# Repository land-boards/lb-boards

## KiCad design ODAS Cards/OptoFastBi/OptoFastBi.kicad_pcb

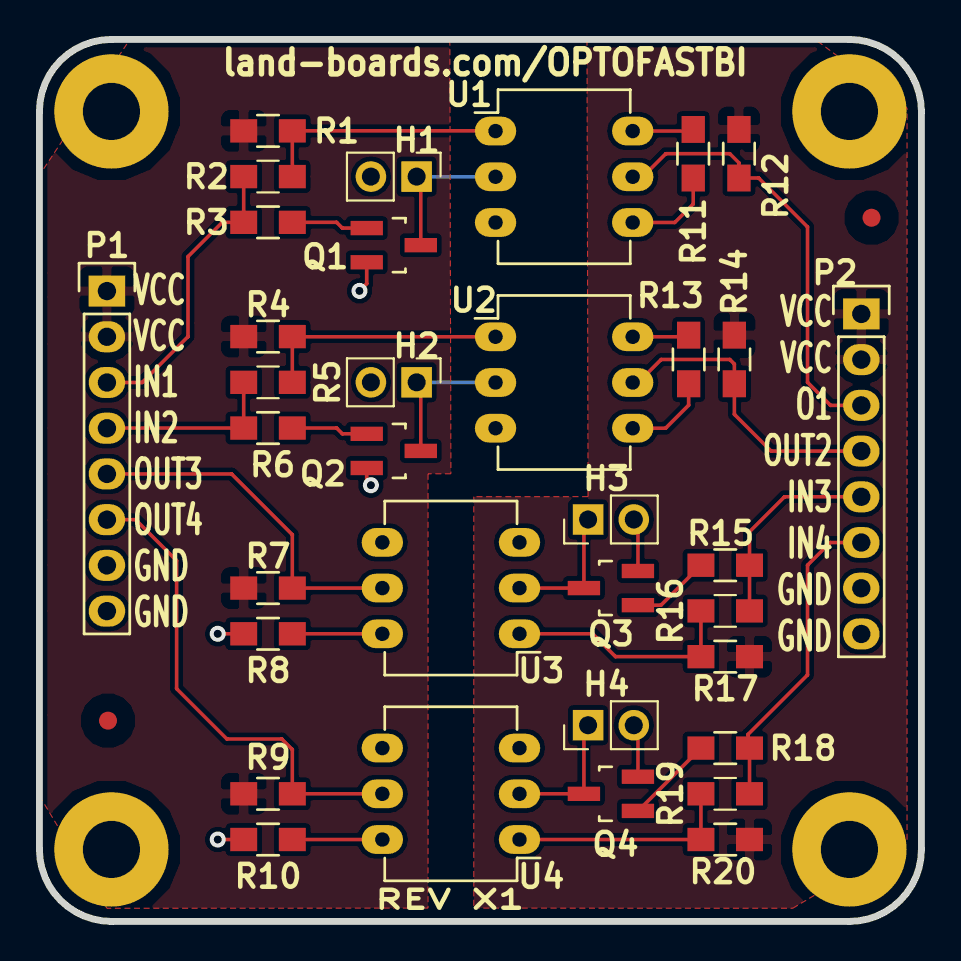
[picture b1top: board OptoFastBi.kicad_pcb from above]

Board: 32 copper layers, 49.0 x 49.0 mm, 41 parts (0 on the bottom side), 28 nets.

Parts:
FID1, FID2: ADAFRUIT_FIDUCIAL; FIDUCIAL
H1, H2, H3, H4: DNP; Pin_Header_Straight_1x02_Pitch2.54mm
MTG1, MTG2, MTG3, MTG4: MTG_HOLE; MTG-4-40
P1, P2: CONN_01X08; Pin_Header_Straight_1x08
Q1, Q2, Q3, Q4: DNP(2N3904); SOT-23_Handsoldering
R1, R4, R17, R20: 150; R_0805_HandSoldering
R2, R5, R16, R19: DNP; R_0805_HandSoldering
R3, R6, R15, R18: 10K; R_0805_HandSoldering
R7, R9, R12, R14: 1.2K; R_0805_HandSoldering
R8, R10, R11, R13: 20K; R_0805_HandSoldering
TEST: COUPON; TEST_BLK-REAR
U1, U2, U3, U4: 4N26; DIP-6_W7.62mm_LongPads

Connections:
/GNDL: H1.2, H2.2, P1.7, P1.8, Q1.2, Q2.2, R8.2, R10.2, U3.4, U4.4
/GNDR: H3.2, H4.2, P2.7, P2.8, Q3.2, Q4.2, R11.2, R13.2, U1.4, U2.4
/IN1: P1.3, R2.1, R3.1
/IN2: P1.4, R5.1, R6.1
/IN3: P2.5, R15.1, R16.1
/IN4: P2.6, R18.1, R19.1
/OUT1: P2.3, R12.1, U1.5
/OUT2: P2.4, R14.1, U2.5
/OUT3: P1.5, R7.1, U3.5
/OUT4: P1.6, R9.1, U4.5
/VCCL: P1.1, P1.2, R1.1, R4.1, R7.2, R9.2
/VCCR: P2.1, P2.2, R12.2, R14.2, R17.1, R20.1
unnamed: H1.1, Q1.3, U1.2
unnamed: H2.1, Q2.3, U2.2
unnamed: H3.1, Q3.3, U3.2
unnamed: H4.1, Q4.3, U4.2
unnamed: Q1.1, R3.2
unnamed: Q2.1, R6.2
unnamed: Q3.1, R15.2
unnamed: Q4.1, R18.2
unnamed: R1.2, R2.2, U1.1
unnamed: R4.2, R5.2, U2.1
unnamed: R8.1, U3.6
unnamed: R10.1, U4.6
unnamed: R11.1, U1.6
unnamed: R13.1, U2.6
unnamed: R16.2, R17.2, U3.1
unnamed: R19.2, R20.2, U4.1

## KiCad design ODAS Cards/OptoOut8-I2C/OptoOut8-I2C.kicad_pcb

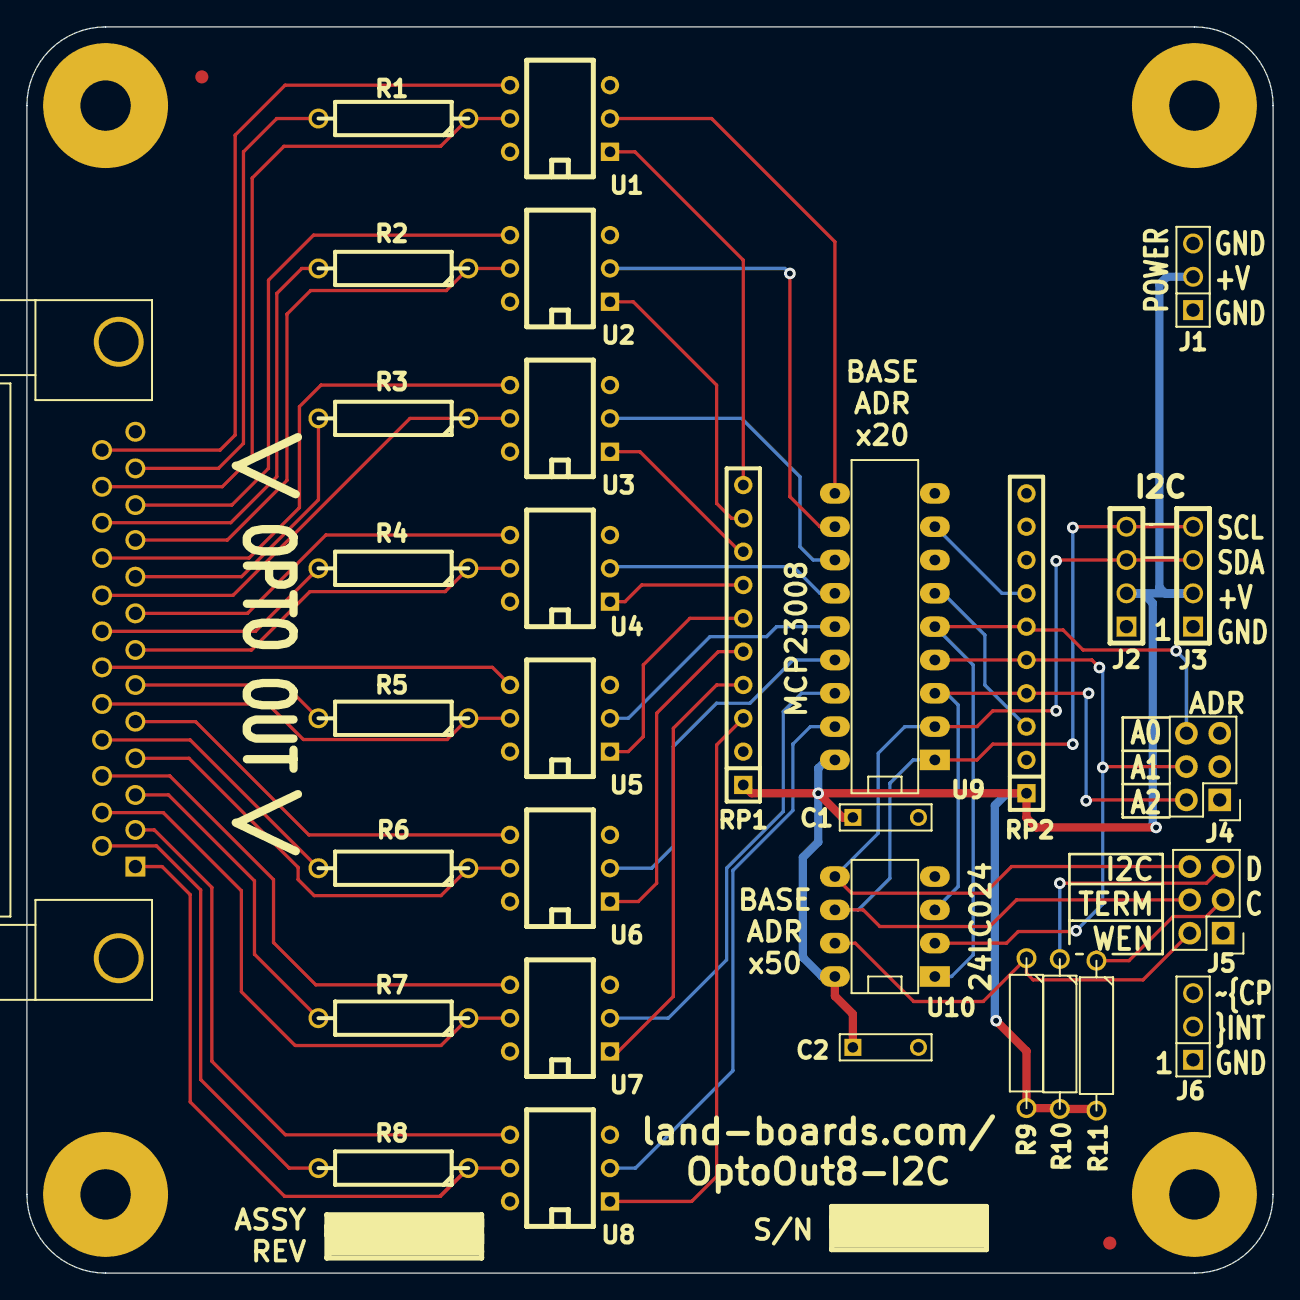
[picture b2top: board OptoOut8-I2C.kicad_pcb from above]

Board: 2 copper layers, 95.0 x 95.0 mm, 40 parts (0 on the bottom side), 52 nets.

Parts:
C1, C2: 0.1uF; C_Rect_L7_W2_P5
FID1, FID2: ADAFRUIT_FIDUCIAL; FIDUCIAL
J1, J6: CONN_3; PIN_ARRAY_3X1
J2, J3: CONN_4; pin_array_4x1
J4: CONN_3X2; Pin_Header_Straight_2x03
J5: CONN_02X03; Pin_Header_Straight_2x03
J7: DB25; DB25FC
MTG1, MTG2, MTG3, MTG4: MTG_HOLE; MTG-6-32
R1, R2, R3, R4, R5, R6, R7, R8: 4.7K; R4-5
R9: 1K; R4-5
R10, R11: 2.2K; R4-5
RP1: 330-RPACK; SIL-10
RP2: 4.7K-RPACK; SIL-10
ST1, ST2: CONN_1; REV_BLOCK
U1, U2, U3, U4, U5, U6, U7, U8: 4N26; DIP-6__300
U9: MCP23008P; DIP-18__300_ELL
U10: 24C01; DIP-8__300_ELL

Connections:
/A0: J4.6, RP2.6, U9.5, U10.1
/A1: J4.4, RP2.5, U9.4, U10.2
/A2: J4.2, RP2.4, U9.3, U10.3
/G0: J7.25, U1.4
/G1: J7.11, U2.4
/G2: J7.22, U3.4
/G3: J7.8, U4.4
/G4: J7.19, U5.4
/G5: J7.5, U6.4
/G6: J7.16, U7.4
/G7: J7.2, U8.4
/S0: J7.24, R1.1, U1.5
/S1: J7.10, R2.1, U2.5
/S2: J7.21, R3.1, U3.5
/S3: J7.7, R4.1, U4.5
/S4: J7.18, R5.1, U5.5
/S5: J7.4, R6.1, U6.5
/S6: J7.15, R7.1, U7.5
/S7: J7.1, R8.1, U8.5
/SCL: J2.4, J3.4, J5.4, U9.1, U10.6
/SDA: J2.3, J3.3, J5.6, U9.2, U10.5
/V0: J7.12, R1.2
/V1: J7.23, R2.2
/V2: J7.9, R3.2
/V3: J7.20, R4.2
/V4: J7.6, R5.2
/V5: J7.17, R6.2
/V6: J7.3, R7.2
/V7: J7.14, R8.2
/VCC: C1.1, C2.1, J1.2, J2.2, J3.2, R9.2, R10.2, R11.2, RP1.1, RP2.1, U9.18, U10.8
GND: C1.2, C2.2, J1.1, J1.3, J2.1, J3.1, J4.1, J4.3, J4.5, J5.1, J6.1, J6.3, U9.9, U10.4
unnamed: J5.2, R9.1, U10.7
unnamed: J5.3, R11.1
unnamed: J5.5, R10.1
unnamed: RP1.3, U8.1
unnamed: RP1.4, U7.1
unnamed: RP1.5, U6.1
unnamed: RP1.6, U5.1
unnamed: RP1.7, U4.1
unnamed: RP1.8, U3.1
unnamed: RP1.9, U2.1
unnamed: RP1.10, U1.1
unnamed: RP2.3, U9.6
unnamed: RP2.7, U9.8
unnamed: U1.2, U9.10
unnamed: U2.2, U9.11
unnamed: U3.2, U9.12
unnamed: U4.2, U9.13
unnamed: U5.2, U9.14
unnamed: U6.2, U9.15
unnamed: U7.2, U9.16
unnamed: U8.2, U9.17

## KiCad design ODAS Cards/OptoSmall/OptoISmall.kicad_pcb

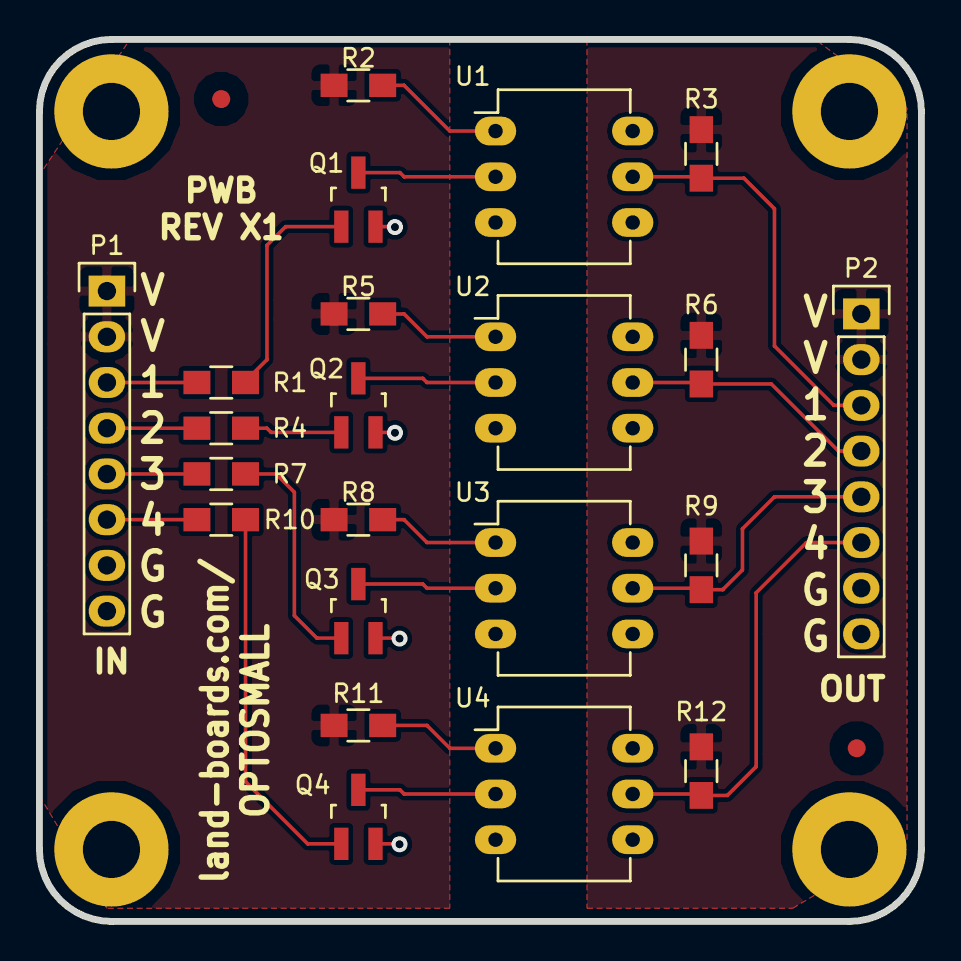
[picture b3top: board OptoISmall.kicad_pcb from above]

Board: 2 copper layers, 49.0 x 49.0 mm, 29 parts (1 on the bottom side), 24 nets.

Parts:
FID1, FID2: ADAFRUIT_FIDUCIAL; FIDUCIAL
MTG1, MTG2, MTG3, MTG4: MTG_HOLE; MTG-4-40
P1, P2: CONN_01X08; Pin_Header_Straight_1x08
Q1, Q2, Q3, Q4: 2N3904; SOT-23_Handsoldering
R1, R4, R7, R10: 10K; R_0805_HandSoldering
R2, R5, R8, R11: 150; R_0805_HandSoldering
R3, R6, R9, R12: 1.2K; R_0805_HandSoldering
ST1: CONN_1; REV_BLOCK
U1, U2, U3, U4: 4N26; DIP-6_W7.62mm_LongPads

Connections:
/OptoBlk1/GND1: P1.7, P1.8, Q1.2, Q2.2, Q3.2, Q4.2
/OptoBlk1/GND2: P2.7, P2.8, U1.4, U2.4, U3.4, U4.4
/OptoBlk1/IN1: P1.3, R1.1
/OptoBlk1/OUT: P2.3, R3.1, U1.5
/OptoBlk1/VCC1: P1.1, P1.2, R2.1, R5.1, R8.1, R11.1
/OptoBlk1/VCC2: P2.1, P2.2, R3.2, R6.2, R9.2, R12.2
/OptoBlk2/IN1: P1.4, R4.1
/OptoBlk2/OUT: P2.4, R6.1, U2.5
/OptoBlk3/IN1: P1.5, R7.1
/OptoBlk3/OUT: P2.5, R9.1, U3.5
/OptoBlk4/IN1: P1.6, R10.1
/OptoBlk4/OUT: P2.6, R12.1, U4.5
unnamed: Q1.1, R1.2
unnamed: Q1.3, U1.2
unnamed: Q2.1, R4.2
unnamed: Q2.3, U2.2
unnamed: Q3.1, R7.2
unnamed: Q3.3, U3.2
unnamed: Q4.1, R10.2
unnamed: Q4.3, U4.2
unnamed: R2.2, U1.1
unnamed: R5.2, U2.1
unnamed: R8.2, U3.1
unnamed: R11.2, U4.1

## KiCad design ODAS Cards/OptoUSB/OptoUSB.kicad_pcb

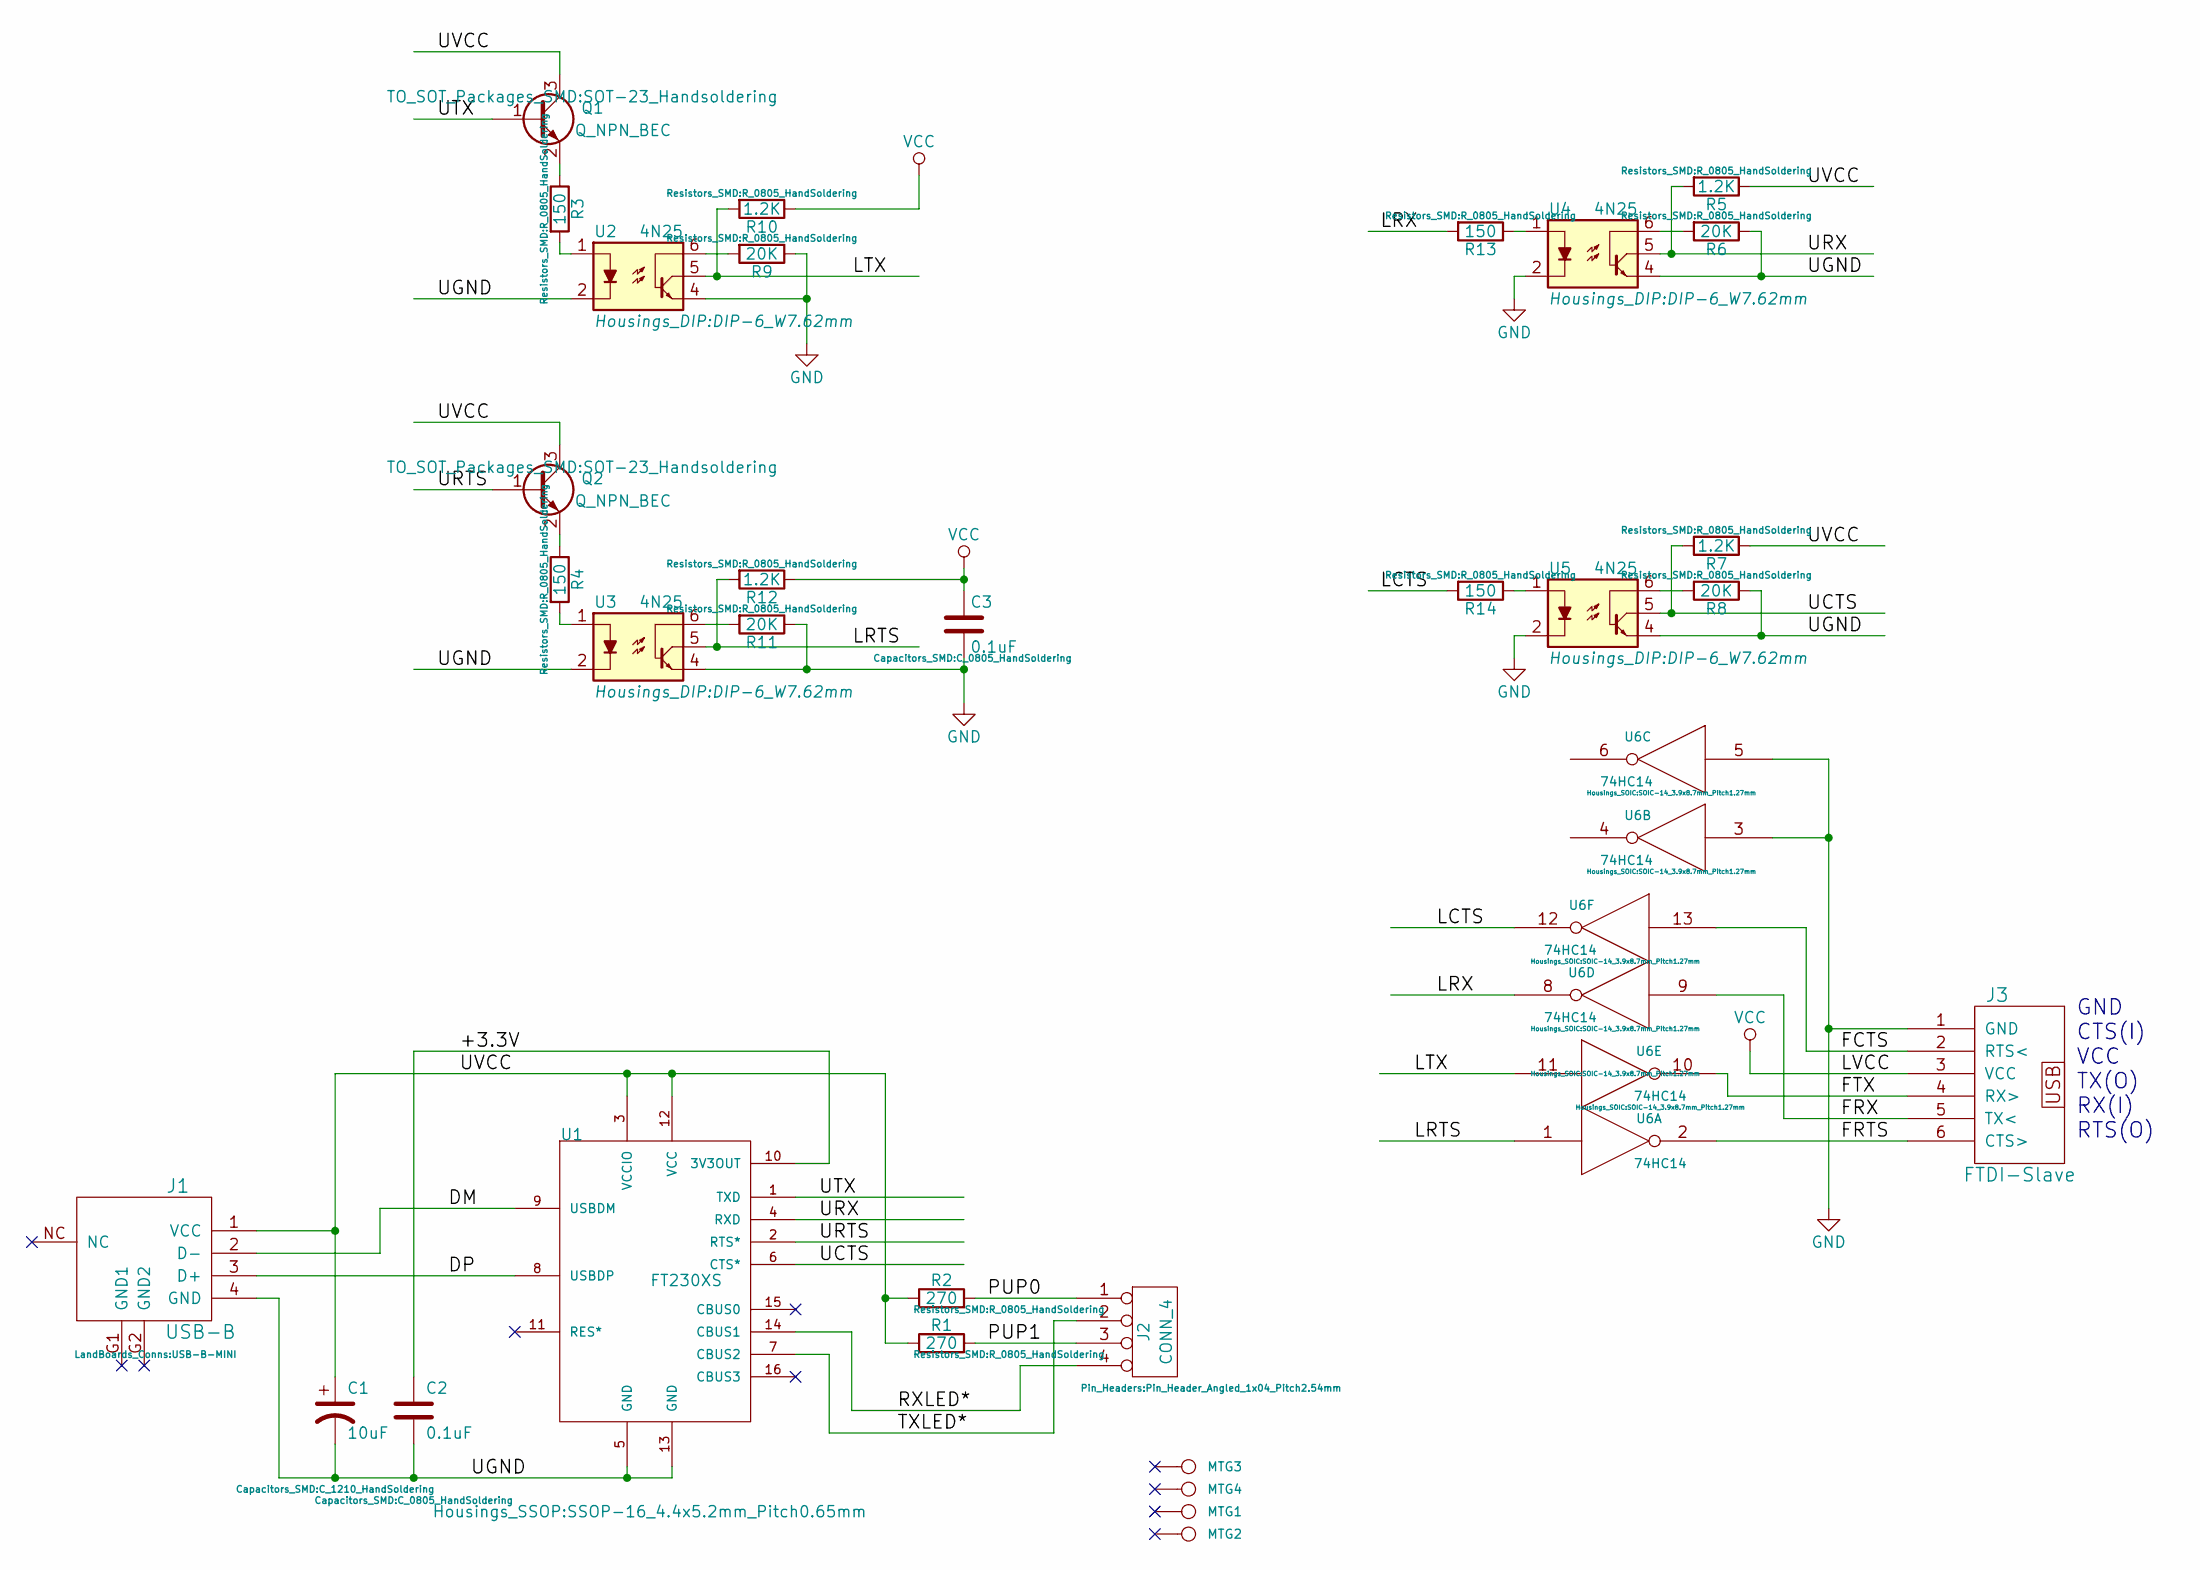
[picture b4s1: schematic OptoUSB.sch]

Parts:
C1: 10uF; C_1210_HandSoldering; MfgPN CC121ZKY5V8BB106
C2: 0.1uF; C_0805_HandSoldering; MfgPN GRM155F51E104ZA1J
C3: 0.1uF; C_0805_HandSoldering
J1: USB-B; USB-B-MINI; MfgPN UX60SC-MB-5ST(80)
J2: CONN_4; Pin_Header_Angled_1x04_Pitch2.54mm
J3: FTDI-Slave
MTG1, MTG3: CONN_1; MTG-4-40; MfgPN N/A
MTG2, MTG4: CONN_1; MTG-4-40
Q1, Q2: Q_NPN_BEC; SOT-23_Handsoldering
R1: 270; R_0805_HandSoldering
R2: 270; R_0805_HandSoldering; MfgPN CRG0805F270R
R3, R4, R13, R14: 150; R_0805_HandSoldering
R5, R7, R10, R12: 1.2K; R_0805_HandSoldering
R6, R8, R9, R11: 20K; R_0805_HandSoldering
U1: FT230XS; SSOP-16_4.4x5.2mm_Pitch0.65mm
U2, U3, U4, U5: 4N25; DIP-6_W7.62mm
U6: 74HC14; SOIC-14_3.9x8.7mm_Pitch1.27mm

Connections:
/+3.3V: C2.1, U1.10 (3V3OUT)
/DM: J1.2 (D-), U1.9 (USBDM)
/DP: J1.3 (D+), U1.8 (USBDP)
/FCTS: J3.2 (RTS<), U6.13
/FRTS: J3.6 (CTS>), U6.2
/FRX: J3.5 (TX<), U6.9
/FTX: J3.4 (RX>), U6.10
/LCTS: R14.2, U6.12
/LRTS: R12.2, U3.5, U6.1
/LRX: R13.2, U6.8
/LTX: R10.2, U2.5, U6.11
/PUP0: J2.1, R2.2
/PUP1: J2.3, R1.2
/RXLED*: J2.4, U1.14 (CBUS1)
/TXLED*: J2.2, U1.7 (CBUS2)
/UCTS: R7.2, U1.6 (CTS*), U5.5
/UGND: C1.2, C2.2, J1.4 (GND), R6.1, R8.1, U1.5 (GND), U1.13 (GND), U2.2, U3.2, U4.4, U5.4
/URTS: Q2.1 (B), U1.2 (RTS*)
/URX: R5.2, U1.4 (RXD), U4.5
/UTX: Q1.1 (B), U1.1 (TXD)
/UVCC: C1.1, J1.1 (VCC), Q1.3 (C), Q2.3 (C), R1.1, R2.1, R5.1, R7.1, U1.3 (VCCIO), U1.12 (VCC)
GND: C3.2, J3.1 (GND), R9.1, R11.1, U2.4, U3.4, U4.2, U5.2, U6.3, U6.5, U6.7 (GND)
unnamed: Q1.2 (E), R3.1
unnamed: Q2.2 (E), R4.1
unnamed: R3.2, U2.1
unnamed: R4.2, U3.1
unnamed: R6.2, U4.6
unnamed: R8.2, U5.6
unnamed: R9.2, U2.6
unnamed: R11.2, U3.6
unnamed: R13.1, U4.1
unnamed: R14.1, U5.1
VCC: C3.1, J3.3 (VCC), R10.1, R12.1, U6.14 (VCC)

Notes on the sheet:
GND CTS(I) VCC TX(O) RX(I) RTS(O)

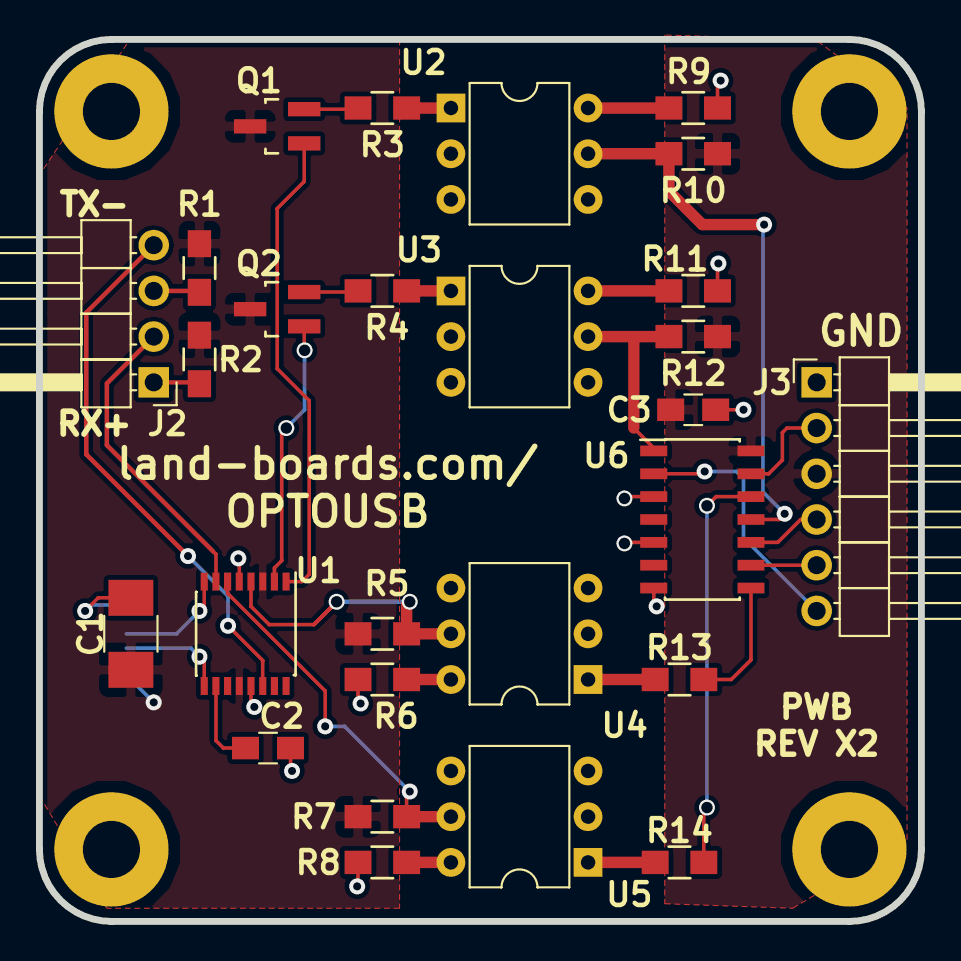
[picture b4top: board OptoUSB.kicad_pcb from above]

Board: 2 copper layers, 49.0 x 49.0 mm, 32 parts (1 on the bottom side), 33 nets.

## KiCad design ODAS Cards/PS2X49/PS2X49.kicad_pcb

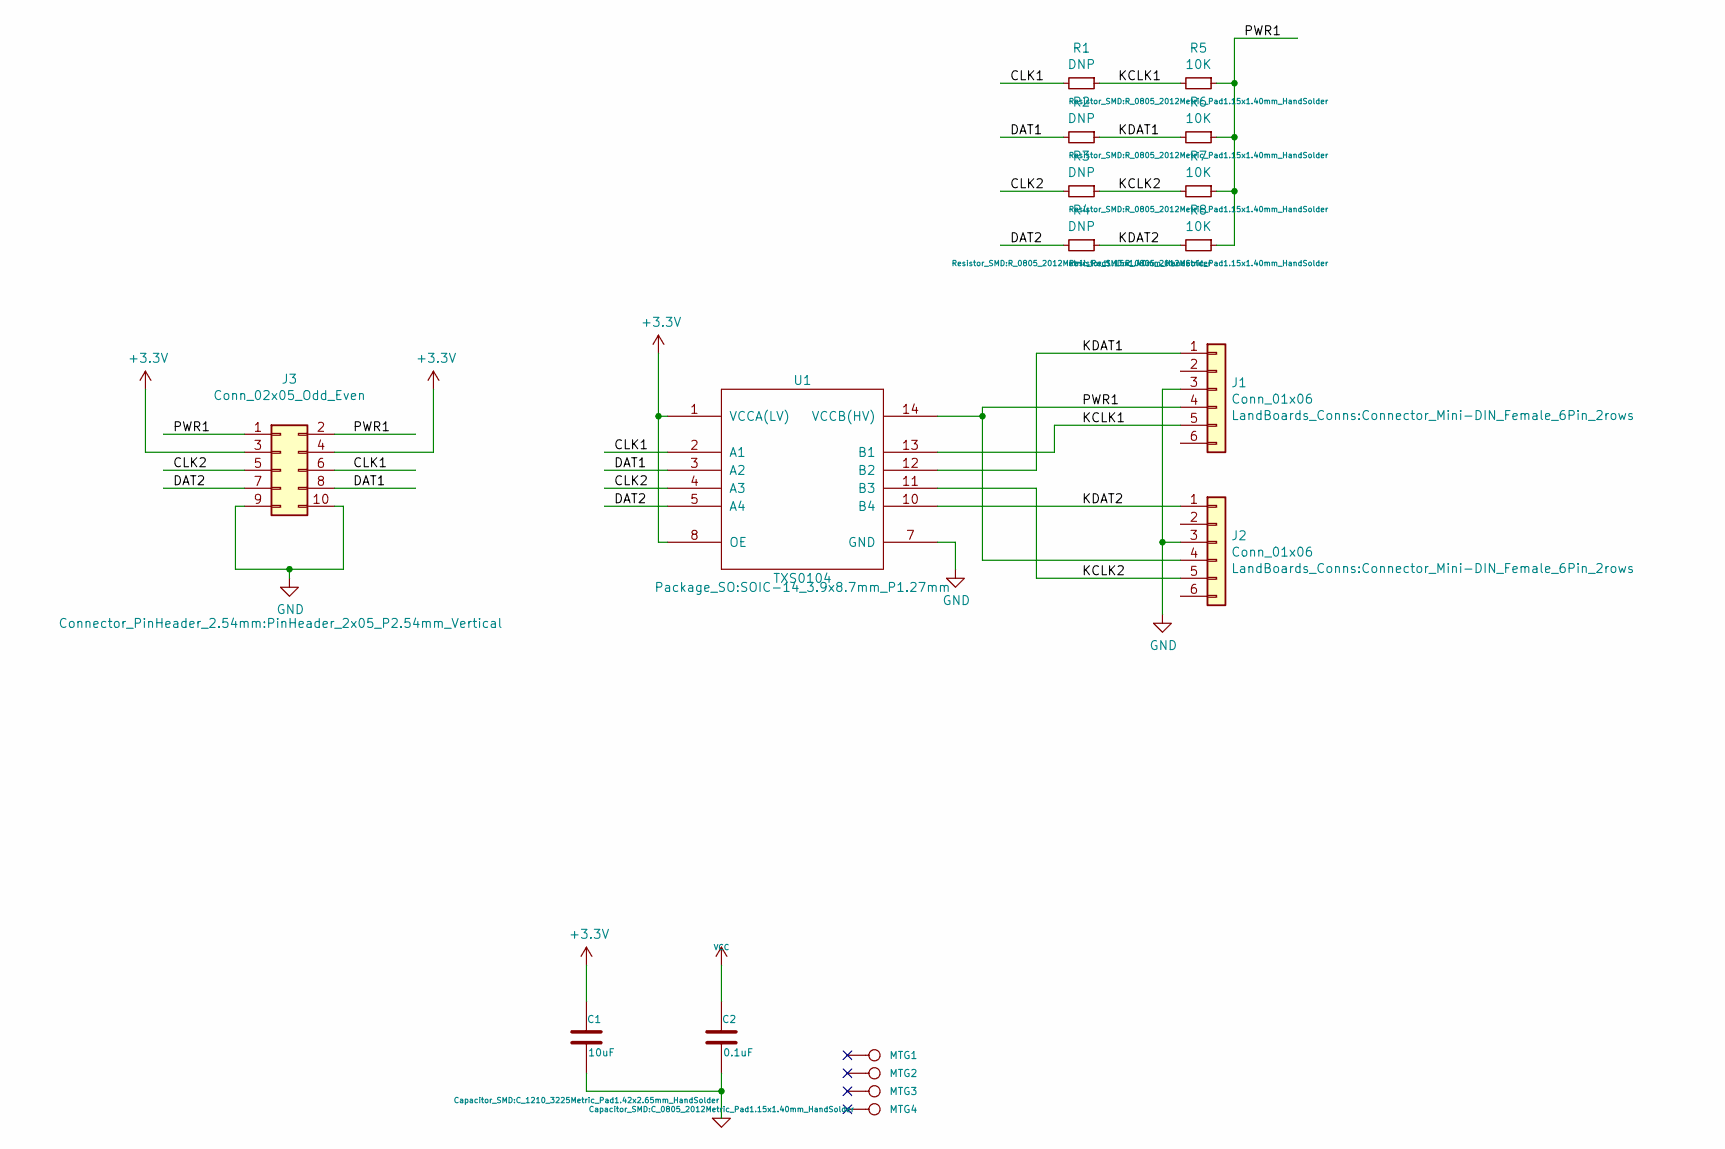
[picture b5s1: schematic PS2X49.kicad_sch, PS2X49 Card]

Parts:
C1: 10uF; C_1210_3225Metric_Pad1.42x2.65mm_HandSolder
C2: 0.1uF; C_0805_2012Metric_Pad1.15x1.40mm_HandSolder
J1, J2: Conn_01x06; Connector_Mini-DIN_Female_6Pin_2rows
J3: Conn_02x05_Odd_Even; PinHeader_2x05_P2.54mm_Vertical
MTG1, MTG2, MTG3, MTG4: CONN_1; MTG-4-40
R1, R2, R3, R4: DNP; R_0805_2012Metric_Pad1.15x1.40mm_HandSolder
R5, R6, R7, R8: 10K; R_0805_2012Metric_Pad1.15x1.40mm_HandSolder
U1: TXS0104; SOIC-14_3.9x8.7mm_P1.27mm

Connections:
+3V3: C1.1, J3.3, J3.4, U1.1 (VCCA(LV)), U1.8 (OE)
/CLK1: J3.6, R1.2, U1.2 (A1)
/CLK2: J3.5, R3.2, U1.4 (A3)
/DAT1: J3.8, R2.2, U1.3 (A2)
/DAT2: J3.7, R4.2, U1.5 (A4)
/KCLK1: J1.5, R1.1, R5.2, U1.13 (B1)
/KCLK2: J2.5, R3.1, R7.2, U1.11 (B3)
/KDAT1: J1.1, R2.1, R6.2, U1.12 (B2)
/KDAT2: J2.1, R4.1, R8.2, U1.10 (B4)
/PWR1: J1.4, J2.4, J3.1, J3.2, R5.1, R6.1, R7.1, R8.1, U1.14 (VCCB(HV))
GND: C1.2, C2.2, J1.3, J2.3, J3.9, J3.10, U1.7 (GND)
VCC: C2.1

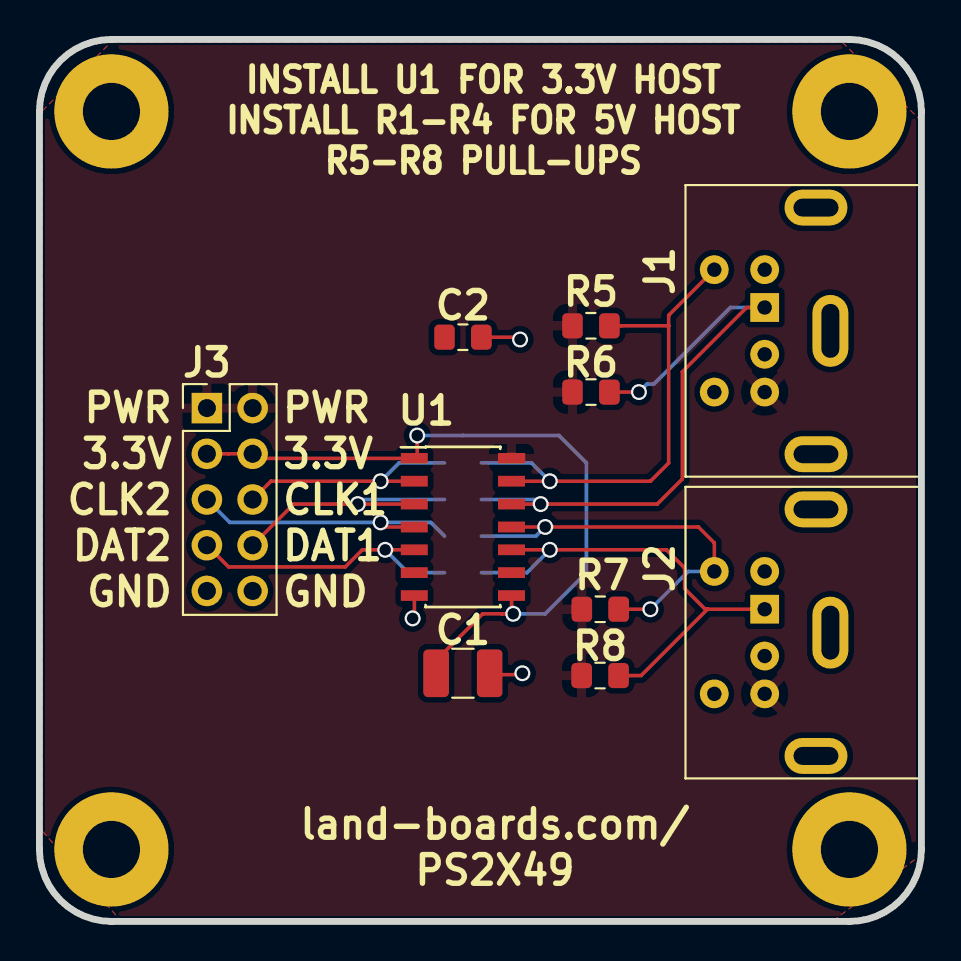
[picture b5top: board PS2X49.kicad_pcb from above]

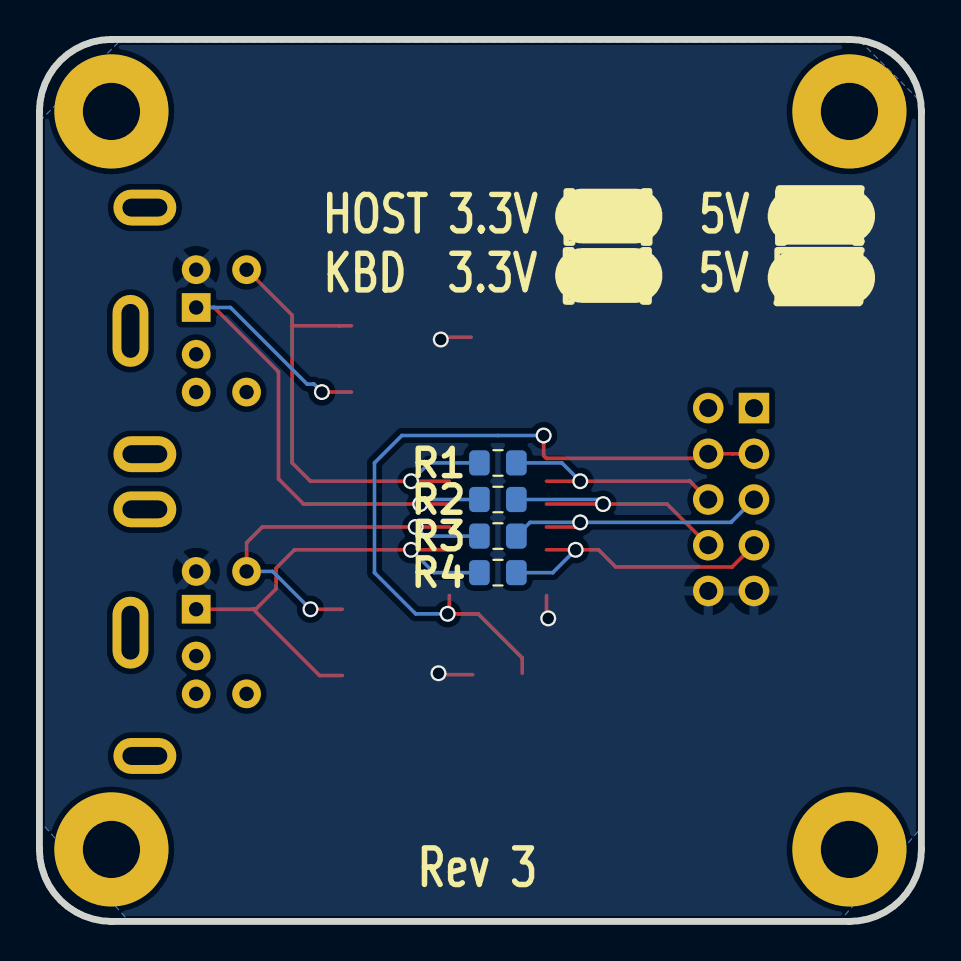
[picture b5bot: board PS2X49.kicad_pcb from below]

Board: 2 copper layers, 49.0 x 49.0 mm, 18 parts (4 on the bottom side), 11 nets.

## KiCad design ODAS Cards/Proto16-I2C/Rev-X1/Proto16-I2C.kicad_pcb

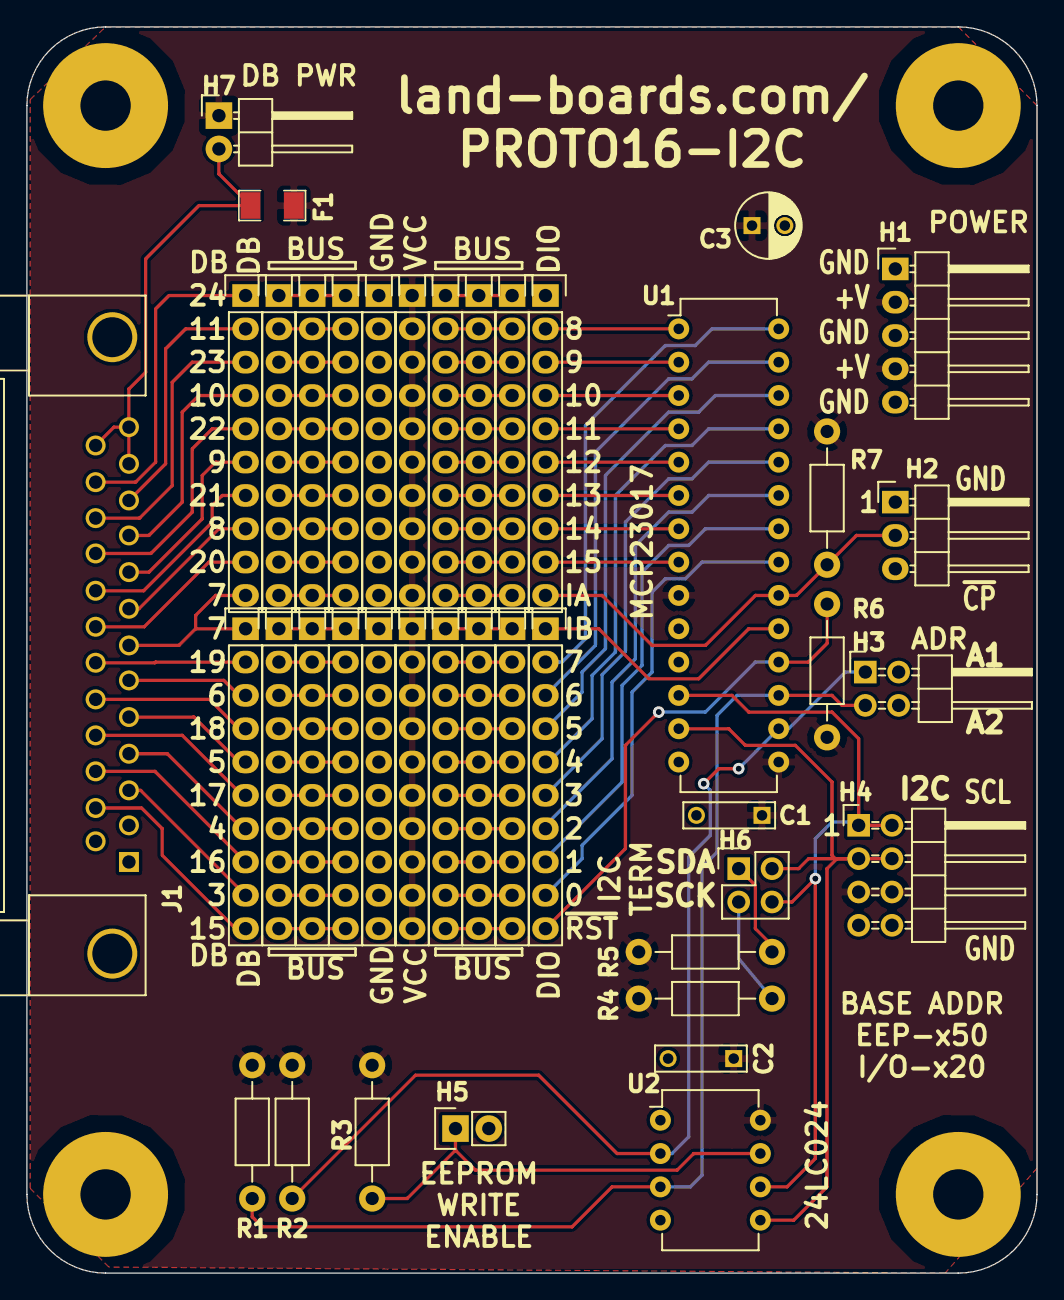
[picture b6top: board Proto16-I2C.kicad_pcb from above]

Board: 2 copper layers, 77.0 x 95.0 mm, 46 parts (0 on the bottom side), 88 nets.

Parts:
C1, C2: 0.1uF; C_Rect_L7_W2_P5
C3: 47uF; C_Radial_D5_L11_P2.5
F1: FUSE; SM1206
H1: CONN_01X05; Pin_Header_Angled_1x05
H2: CONN_01X03; Pin_Header_Angled_1x03
H3: CONN_02X02; Pin_Header_Angled_2x02
H4: CONN_02X04; Pin_Header_Angled_2x04
H5: CONN_01X02; Pin_Header_Straight_1x02
H6: CONN_02X02; Pin_Header_Straight_2x02
H7: CONN_01X02; Pin_Header_Angled_1x02
J1: DB25; DB25FC
MTG1, MTG2, MTG3, MTG4: MTG_HOLE; MTG-6-32
P1, P3, P4, P5, P6, P7, P8, P9, P10, P11, P12, P13, P14, P15, P16, P17, P18, P19, P20, P99: CONN_01X10; Pin_Header_Straight_1x10
R1, R2, R6, R7: 10K; Resistor_Horizontal_RM10mm
R3: 1K; Resistor_Horizontal_RM10mm
R4, R5: 2.2K; Resistor_Horizontal_RM10mm
TESTED: TESTED_COUPON; TEST_BLK-REAR
U1: MCP23017P; DIP-28_W7.62mm
U2: 24C01; DIP-8_W7.62mm

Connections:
+5V: C1.1, C2.1, C3.1, F1.1, H1.2, H1.4, H4.5, H4.6, H7.1, P5.1, P5.2, P5.3, P5.4, P5.5, P5.6, P5.7, P5.8, P5.9, P5.10, P6.1, P6.2, P6.3, P6.4, P6.5, P6.6, P6.7, P6.8, P6.9, P6.10, R1.2, R2.2, R3.2, R4.2, R5.2, R6.2, R7.2, U1.9, U1.15, U2.8
/A1: H3.1, R2.1, U1.16, U2.2
/A2: H3.3, R1.1, U1.17, U2.3
/B3: J1.3, P18.9
/B4: J1.4, P18.7
/B5: J1.5, P18.5
/B6: J1.6, P18.3
/B7: J1.7, P17.10, P18.1
/B8: J1.8, P17.8
/B9: J1.9, P17.6
/B10: J1.10, P17.4
/B11: J1.11, P17.2
/B15: J1.15, P18.10
/B16: J1.16, P18.8
/B17: J1.17, P18.6
/B18: J1.18, P18.4
/B19: J1.19, P18.2
/B20: J1.20, P17.9
/B21: J1.21, P17.7
/B22: J1.22, P17.5
/B23: J1.23, P17.3
/B24: J1.24, P17.1
/G0: P19.9, U1.21
/G1: P19.8, U1.22
/G2: P19.7, U1.23
/G3: P19.6, U1.24
/G4: P19.5, U1.25
/G5: P19.4, U1.26
/G6: P19.3, U1.27
/G7: P19.2, U1.28
/G8: P20.2, U1.1
/G9: P20.3, U1.2
/G10: P20.4, U1.3
/G11: P20.5, U1.4
/G12: P20.6, U1.5
/G13: P20.7, U1.6
/G14: P20.8, U1.7
/G15: P20.9, U1.8
/IA: H2.2, P20.10, R7.1, U1.20
/IB: P19.1, U1.19
/RST: P19.10, R6.1, U1.18
/SCL: H4.1, H4.2, H6.4, U1.12, U2.6
/SDA: H4.3, H4.4, H6.2, U1.13, U2.5
GND: C1.2, C2.2, C3.2, H1.1, H1.3, H1.5, H2.1, H2.3, H3.2, H3.4, H4.7, H4.8, H5.2, J1.1, J1.2, J1.14, P8.1, P8.2, P8.3, P8.4, P8.5, P8.6, P8.7, P8.8, P8.9, P8.10, P9.1, P9.2, P9.3, P9.4, P9.5, P9.6, P9.7, P9.8, P9.9, P9.10, U1.10, U2.1, U2.4
unnamed: F1.2, H7.2, J1.12, J1.13, J1.25
unnamed: H5.1, R3.1, U2.7
unnamed: H6.1, R5.1
unnamed: H6.3, R4.1
unnamed: P1.1, P3.1, P7.1
unnamed: P1.2, P3.2, P7.2
unnamed: P1.3, P3.3, P7.3
unnamed: P1.4, P3.4, P7.4
unnamed: P1.5, P3.5, P7.5
unnamed: P1.6, P3.6, P7.6
unnamed: P1.7, P3.7, P7.7
unnamed: P1.8, P3.8, P7.8
unnamed: P1.9, P3.9, P7.9
unnamed: P1.10, P3.10, P7.10
unnamed: P4.1, P10.1, P99.1
unnamed: P4.2, P10.2, P99.2
unnamed: P4.3, P10.3, P99.3
unnamed: P4.4, P10.4, P99.4
unnamed: P4.5, P10.5, P99.5
unnamed: P4.6, P10.6, P99.6
unnamed: P4.7, P10.7, P99.7
unnamed: P4.8, P10.8, P99.8
unnamed: P4.9, P10.9, P99.9
unnamed: P4.10, P10.10, P99.10
unnamed: P11.1, P13.1, P16.1
unnamed: P11.2, P13.2, P16.2
unnamed: P11.3, P13.3, P16.3
unnamed: P11.4, P13.4, P16.4
unnamed: P11.5, P13.5, P16.5
unnamed: P11.6, P13.6, P16.6
unnamed: P11.7, P13.7, P16.7
unnamed: P11.8, P13.8, P16.8
unnamed: P11.9, P13.9, P16.9
unnamed: P11.10, P13.10, P16.10
unnamed: P12.1, P14.1, P15.1
unnamed: P12.2, P14.2, P15.2
unnamed: P12.3, P14.3, P15.3
unnamed: P12.4, P14.4, P15.4
unnamed: P12.5, P14.5, P15.5
unnamed: P12.6, P14.6, P15.6
unnamed: P12.7, P14.7, P15.7
unnamed: P12.8, P14.8, P15.8
unnamed: P12.9, P14.9, P15.9
unnamed: P12.10, P14.10, P15.10
